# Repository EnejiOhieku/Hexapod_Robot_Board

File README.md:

# 18-DOF Hexapod Robot Controller Board (Rev 3.0)

[-brightgreen.svg)](reports/Hexapod_Robot_Board-erc.rpt)
[-brightgreen.svg)](reports/Hexapod_Robot_Board-drc.rpt)

A production-ready, high-power 4-layer robotics controller PCB designed for an **18-DOF Hexapod Robot**. Rev 3.0 is a major architectural upgrade introducing a **dedicated Vision Coprocessor** (second ESP32-S3-WROOM-1U-N8R8), a **BQ25886 2S LiPo fast charger** (replaces TP5100), **triple South-edge USB Type-C ports** (dedicated charging, main MCU, and vision MCU), an **OV3660/OV2640 DVP camera interface** with a 1–3W illumination LED driver, a **Sipeed MaixSense A010 3D ToF** sensor on a fully isolated 5V rail, a **dedicated Vision 3.3V ultra-low-noise LDO**, and an **external power switch connector**. The locomotion subsystem retains the proven dual 5A XL4015 buck split-rail architecture and dual PCA9685 uncrossed PWM routing.

---

## 3D Board Previews

---

## System Architecture (Rev 3.0)

```mermaid
flowchart TD
    subgraph Power["Power & Battery Management"]
        J_CHG["USB Type-C (J_CHG) — Dedicated 2S Charger"] --> U2["BQ25886 2S LiPo Charger (8.4V / 1.5A)"]
        BAT["2S LiPo Battery (XT30PW, South Edge)"] --> SW["Main Power Switch (SW_PWR)"]
        U2 --> BAT
        SW --> VBAT_SW["Switched Battery Bus (VBAT_SW)"]
        VBAT_SW --> BUCK_L["Left Buck (XL4015, 5V / 5A) — U3_L"]
        VBAT_SW --> BUCK_R["Right Buck (XL4015, 5V / 5A) — U3_R"]
        VBAT_SW --> U4["Main 3.3V LDO (AP2112K / AMS1117-3.3) — U4"]
        VBAT_SW --> U_LDO_VIS["Vision 3.3V LDO (AMS1117-3.3) — U_LDO_VIS"]
        VBAT_SW --> U_REG_5V_TOF["Dedicated 5V ToF Regulator (AMS1117-5.0) — U_REG_5V_TOF"]
        VBAT_SW --> DIV["Battery Voltage Divider (R_DIV1 / R_DIV2)"]
    end

    subgraph Locomotion["Main Locomotion Controller (U1 — ESP32-S3-WROOM-1U)"]
        J_USB_MAIN["USB Type-C (J2) — Native USB / JTAG"] --> U1["ESP32-S3-WROOM-1U (Top-Right Edge, IPEX U.FL)"]
        U4 --> U1
        U1 -- "I2C (GPIO1/41)" --> U5["PCA9685 Left (0x40) — U5"]
        U1 -- "I2C (GPIO1/41)" --> U6["PCA9685 Right (0x41) — U6"]
        U1 -- "I2C (GPIO1/41)" --> U7["MPU-6050 6-Axis IMU (Centre, 0x68) — U7"]
        U7 -- "MPU_INT (GPIO10)" --> U1
        DIV -- "ADC (GPIO5)" --> U1
        U1 -- "GPIO48" --> LED_RGB_MAIN["WS2812B-2020 Status NeoPixel"]
    end

    subgraph Vision["Vision Coprocessor (U8 — ESP32-S3-WROOM-1U-N8R8)"]
        J_USB_VIS["USB Type-C (J3) — Vision USB / JTAG"] --> U8["ESP32-S3-WROOM-1U-N8R8 (Top-Left Edge, IPEX U.FL)"]
        U_LDO_VIS --> U8
        U8 -- "24-Pin 8-bit DVP (GPIO6-13, 15-18)" --> CAM["OV3660 / OV2640 Camera (J_CAM)"]
        U8 -- "SCCB I2C1 (GPIO4/5)" --> CAM
        U8 -- "UART1 (GPIO1/2)" --> TOF["Sipeed MaixSense A010 3D ToF (J_TOF)"]
        U8 -- "GPIO3 → R_CAM_LED → Q_CAM_LED" --> CAM_LED["1–3W Camera LED (J_CAM_LED)"]
        U_REG_5V_TOF -- "+5V_TOF (Isolated from Servos)" --> TOF
    end

    U1 <==>|"Inter-MCU Full-Duplex UART (GPIO43/44) + Frame Sync IRQ"| U8

    subgraph Servos["Servo Actuation (Split Left/Right Rails)"]
        BUCK_L --> V_SERVO_L["V_SERVO_L Plane (In2.Cu West)"]
        BUCK_R --> V_SERVO_R["V_SERVO_R Plane (In2.Cu East)"]
        U5 -- "PWM 0–11" --> SL["Left Legs 4, 5, 6 (9 Servos) + AUX 4–6"]
        U6 -- "PWM 0–11" --> SR["Right Legs 1, 2, 3 (9 Servos) + AUX 1–3"]
        V_SERVO_L --> SL
        V_SERVO_R --> SR
    end
```

---

## Key Hardware Features

### Dual-MCU Architecture
- **Main Locomotion MCU (`U1`)**: ESP32-S3-WROOM-1U — Dual-core Xtensa LX7 @ 240 MHz, 2.4 GHz Wi-Fi, BLE 5, 16 MB Flash. Placed on the **Top-Right edge** (`X=88.0, Y=2.5 mm`) with IPEX U.FL antenna facing North.
- **Vision Coprocessor (`U8`)**: ESP32-S3-WROOM-1U-N8R8 — Identical SoC, 8 MB PSRAM (Octal), pin-compatible with Zephyr's `esp32s3_eye` board definition. Placed on the **Top-Left edge** (`X=22.0, Y=2.5 mm`) with IPEX U.FL facing North.
- **Inter-MCU Link**: Full-duplex UART (`U1` GPIO43/44 ↔ `U8` GPIO43/44) at up to 3 Mbps, plus hardware Frame Sync / Alert IRQ (`U8` GPIO21 → `U1` GPIO4).

### Vision & Perception
- **Camera Interface**: 24-pin DVP FPC connector (`J_CAM`, top-centre `X=55.0, Y≈-11.0 mm`, rotated 180°) for OV3660 (3 MP) or OV2640 (2 MP). SCCB I²C via 4.7 kΩ pull-ups (`R_CAM_SCL`, `R_CAM_SDA`).
- **3D ToF Sensor**: Sipeed MaixSense A010 connector (`J_TOF`) at `(5.0, -11.0) mm`, powered by an isolated `+5V_TOF` linear rail with >60 dB PSRR to eliminate servo switching noise.
- **Camera Illumination**: 1–3 W white LED driver via AO3400A N-MOSFET (`Q_CAM_LED`), gate driven by Vision GPIO3 through 100 Ω series (`R_CAM_LED`) + 10 kΩ pull-down (`R_PD_CAM_LED`). External LED connector: `J_CAM_LED`.
- **Status NeoPixel**: WS2812B-2020 (`LED_RGB_MAIN`) driven by Main MCU GPIO48 via 330 Ω damping resistor (`R_NEO`).

### Power Architecture
| Rail | Source | Voltage | Max Current | Consumer |
|:---|:---|:---|:---|:---|
| `+VBAT` | 2S LiPo XT30PW | 6.0–8.4 V | 20 A peak | Raw battery |
| `VBAT_SW` | SW_PWR / J_SW_EXT | 6.0–8.4 V | 15 A | All regulators |
| `V_SERVO_L` | XL4015 Buck L (`U3_L`) | 5.0 V | 5 A cont. / 6 A pk | Left legs + AUX 4–6 |
| `V_SERVO_R` | XL4015 Buck R (`U3_R`) | 5.0 V | 5 A cont. / 6 A pk | Right legs + AUX 1–3 |
| `+3V3` | AP2112K LDO (`U4`) | 3.3 V | 600 mA | Main MCU, PCA9685s, IMU |
| `+3V3_VIS` | AMS1117-3.3 (`U_LDO_VIS`) | 3.3 V | 800 mA | Vision MCU, camera |
| `+5V_TOF` | AMS1117-5.0 (`U_REG_5V_TOF`) | 5.0 V | 800 mA | MaixSense A010 ToF (isolated) |
| `VBUS` | USB-C (`J_CHG`) | 5.0 V | 2.0 A | BQ25886 charger input |

- **Battery Management**: BQ25886 (VQFN-24) 2S LiPo fast charger — replaces TP5100. Supports USB BC1.2 detection, USB OTG boost, PowerPath management. Charge/standby LEDs: `LED_CHG`, `LED_FULL`.
- **External Power Switch**: 2-pin header `J_SW_EXT` allows robot chassis-mounted latching switch to gate `VBAT_SW`. Battery charges safely with electronics fully off.

### Triple South-Edge USB-C
All three USB-C receptacles co-located along the South board edge for a single chassis port bay cutout:
1. **`J_CHG` (`J1`, X≈37 mm)** — Dedicated 2S fast charger input. Zero data lines.
2. **`J_USB_MAIN` (`J2`, X≈95.5 mm)** — Main ESP32-S3 native USB / JTAG / gait telemetry.
3. **`J_USB_VISION` (`J3`, X≈84 mm)** — Vision ESP32-S3 native USB / JTAG / video stream.

### Inertial Measurement Unit
- **MPU-6050** (`U7`) at exact geometric centre of mass (`X=55.0, Y=45.0 mm`) with hardware interrupt to Main MCU GPIO10.

### Physical Specifications
- **Dimensions**: 110.0 × 90.0 mm, 3.0 mm corner radii.
- **Mounting**: 4× M3 holes (3.2 mm drill / 6.0 mm pad) at `(5,5)`, `(105,5)`, `(5,85)`, `(105,85)` mm.
- **Stackup**: 4-layer — `F.Cu` signals/PDN · `In1.Cu` solid GND · `In2.Cu` split `V_SERVO` planes · `B.Cu` GND flood/signals.

---

## Servo Channel Mapping

| Joint / Channel | Header | Controller | Ch | I²C Addr | Rail |
|:---|:---|:---|:---|:---|:---|
| **Right Front (RF) Coxa** | `J_L1_C` | PCA9685 Right (`U6`) | PWM 0 | `0x41` | `V_SERVO_R` |
| **Right Front (RF) Femur** | `J_L1_F` | PCA9685 Right (`U6`) | PWM 1 | `0x41` | `V_SERVO_R` |
| **Right Front (RF) Tibia** | `J_L1_T` | PCA9685 Right (`U6`) | PWM 2 | `0x41` | `V_SERVO_R` |
| **Right Middle (RM) Coxa** | `J_L2_C` | PCA9685 Right (`U6`) | PWM 3 | `0x41` | `V_SERVO_R` |
| **Right Middle (RM) Femur** | `J_L2_F` | PCA9685 Right (`U6`) | PWM 4 | `0x41` | `V_SERVO_R` |
| **Right Middle (RM) Tibia** | `J_L2_T` | PCA9685 Right (`U6`) | PWM 5 | `0x41` | `V_SERVO_R` |
| **Right Rear (RR) Coxa** | `J_L3_C` | PCA9685 Right (`U6`) | PWM 6 | `0x41` | `V_SERVO_R` |
| **Right Rear (RR) Femur** | `J_L3_F` | PCA9685 Right (`U6`) | PWM 7 | `0x41` | `V_SERVO_R` |
| **Right Rear (RR) Tibia** | `J_L3_T` | PCA9685 Right (`U6`) | PWM 8 | `0x41` | `V_SERVO_R` |
| **Left Front (LF) Coxa** | `J_L4_C` | PCA9685 Left (`U5`) | PWM 0 | `0x40` | `V_SERVO_L` |
| **Left Front (LF) Femur** | `J_L4_F` | PCA9685 Left (`U5`) | PWM 1 | `0x40` | `V_SERVO_L` |
| **Left Front (LF) Tibia** | `J_L4_T` | PCA9685 Left (`U5`) | PWM 2 | `0x40` | `V_SERVO_L` |
| **Left Middle (LM) Coxa** | `J_L5_C` | PCA9685 Left (`U5`) | PWM 3 | `0x40` | `V_SERVO_L` |
| **Left Middle (LM) Femur** | `J_L5_F` | PCA9685 Left (`U5`) | PWM 4 | `0x40` | `V_SERVO_L` |
| **Left Middle (LM) Tibia** | `J_L5_T` | PCA9685 Left (`U5`) | PWM 5 | `0x40` | `V_SERVO_L` |
| **Left Rear (LR) Coxa** | `J_L6_C` | PCA9685 Left (`U5`) | PWM 6 | `0x40` | `V_SERVO_L` |
| **Left Rear (LR) Femur** | `J_L6_F` | PCA9685 Left (`U5`) | PWM 7 | `0x40` | `V_SERVO_L` |
| **Left Rear (LR) Tibia** | `J_L6_T` | PCA9685 Left (`U5`) | PWM 8 | `0x40` | `V_SERVO_L` |
| **Auxiliary PWM 1–3** | `J_AUX1–3` | PCA9685 Right (`U6`) | PWM 9–11 | `0x41` | `V_SERVO_R` |
| **Auxiliary PWM 4–6** | `J_AUX4–6` | PCA9685 Left (`U5`) | PWM 9–11 | `0x40` | `V_SERVO_L` |

---

## GPIO Assignments

### Main Locomotion MCU (`U1` — ESP32-S3-WROOM-1U)
| GPIO | Function | Direction | Connected To |
|:---|:---|:---|:---|
| GPIO1 | I2C SCL | Output | PCA9685 L/R, MPU-6050 |
| GPIO41 | I2C SDA | Bidirectional | PCA9685 L/R, MPU-6050 |
| GPIO4 | Frame Sync IRQ | Input | Vision MCU GPIO21 |
| GPIO5 | Battery ADC | Input | `R_DIV1`/`R_DIV2` voltage divider |
| GPIO6 | CHG_STAT | Input | BQ25886 `STAT` pin |
| GPIO7 | CHG_PG | Input | BQ25886 `PG` pin (Power Good) |
| GPIO10 | MPU_INT | Input | MPU-6050 INT |
| GPIO19/20 | USB D-/D+ | Bidirectional | `J_USB_MAIN` (J2) |
| GPIO43 | Inter-MCU TX | Output | Vision MCU GPIO44 |
| GPIO44 | Inter-MCU RX | Input | Vision MCU GPIO43 |
| GPIO48 | NeoPixel Data | Output | `R_NEO` → `LED_RGB_MAIN` |

### Vision Coprocessor (`U8` — ESP32-S3-WROOM-1U-N8R8)
| GPIO | Function | Direction | Connected To |
|:---|:---|:---|:---|
| GPIO1 | ToF UART RX | Input | A010 TX (UART1) |
| GPIO2 | ToF UART TX | Output | A010 RX (UART1) |
| GPIO3 | Camera LED PWM | Output | `R_CAM_LED` → `Q_CAM_LED` gate |
| GPIO4 | SCCB SDA (I2C1) | Bidirectional | Camera SIOD, 4.7 kΩ pull-up |
| GPIO5 | SCCB SCL (I2C1) | Output | Camera SIOC, 4.7 kΩ pull-up |
| GPIO6 | DVP VSYNC | Input | Camera VSYNC |
| GPIO7 | DVP HREF | Input | Camera HREF |
| GPIO8–13 | DVP D2–D7 | Input | Camera Y4–Y9 |
| GPIO15 | DVP XCLK | Output | Camera XCLK (10–24 MHz) |
| GPIO16–18 | DVP D0–D2 | Input | Camera Y2–Y4 |
| GPIO19/20 | USB D-/D+ | Bidirectional | `J_USB_VISION` (J3) |
| GPIO21 | Frame Sync IRQ | Output | Main MCU GPIO4 |
| GPIO38 | Camera PWDN | Output | Camera PWDN, 10 kΩ pull-down |
| GPIO43 | Inter-MCU TX | Output | Main MCU GPIO44 |
| GPIO44 | Inter-MCU RX | Input | Main MCU GPIO43 |

---

## Project Structure

```
Hexapod_Robot_Board/
├── Hexapod_Robot_Board.kicad_pro       # Master KiCad 10.0.6 project file
├── Hexapod_Robot_Board.kicad_sch       # Rev 3.0 schematic (dual-MCU, triple USB-C)
├── Hexapod_Robot_Board.kicad_pcb       # 4-layer routed PCB layout
├── Hexapod_Robot_Board.net             # Complete netlist (98 nets)
├── README.md                           # This document
├── 3dmodels/                           # Custom 3D STEP component packages
│   ├── ESP32-S3-WROOM-1U.step
│   ├── MPU-6050.step
│   ├── LED_WS2812B-2020.step
│   └── Hirose_FH12-24S-0.5SH_1x24-1MP_P0.50mm_Horizontal.step
├── fabrication/                        # Manufacturing deliverable package
│   ├── Hexapod_Robot_Board-gerbers.zip
│   ├── Hexapod_Robot_Board-cpl-jlcpcb.csv
│   ├── Hexapod_Robot_Board-bom-jlcpcb.csv
│   ├── Hexapod_Robot_Board.step
│   ├── Hexapod_Robot_Board_Schematic.pdf
│   └── *.png                           # 2D + 3D renders
├── reports/                            # Verification reports
│   ├── Hexapod_Robot_Board-drc.rpt
│   ├── Hexapod_Robot_Board-erc.rpt
│   └── Hexapod_Robot_Board-stats.txt
└── scripts/                            # Python automation suite
    ├── export_fabrication.py           # One-click manufacturing pipeline
    ├── run_final_perfect_route.py      # Freerouting solver
    └── README.md
```

---

## Verification & Compliance

- **ERC**: Passed — **0 errors, 0 warnings** ([`reports/Hexapod_Robot_Board-erc.rpt`](reports/Hexapod_Robot_Board-erc.rpt)).
- **DRC**: Passed — **0 violations, 0 unconnected items** ([`reports/Hexapod_Robot_Board-drc.rpt`](reports/Hexapod_Robot_Board-drc.rpt)).
- **Manufacturability**: JLCPCB / PCBWay 4-layer standard constraints (0.15 mm clearance, 0.20 mm min track, 0.30 mm min drill, 45° mitered geometry).

---

## Revision History

| Rev | Date | Summary |
|:---|:---|:---|
| **3.0** | 2026-10-04 | Vision Coprocessor (ESP32-S3-WROOM-1U-N8R8), BQ25886 2S charger, triple South USB-C, DVP camera, MaixSense A010 ToF on isolated +5V rail, dedicated Vision 3.3V LDO, camera LED driver, inter-MCU UART link, external power switch header, WS2812B NeoPixel. Schematic/PCB annotated and synced. |
| **2.0** | 2026-10-01 | ESP32-S3-WROOM-1U, dual XL4015 5A buck split rails, MPU-6050 at CoM, South-edge USB-C charging via TP5100, dual PCA9685 uncrossed PWM, 4-layer routing, 0 DRC/ERC. |
| **1.0** | 2026-09-28 | Initial 18-DOF hexapod controller. ESP32-S3, single buck, TP5100 charger, dual PCA9685. |

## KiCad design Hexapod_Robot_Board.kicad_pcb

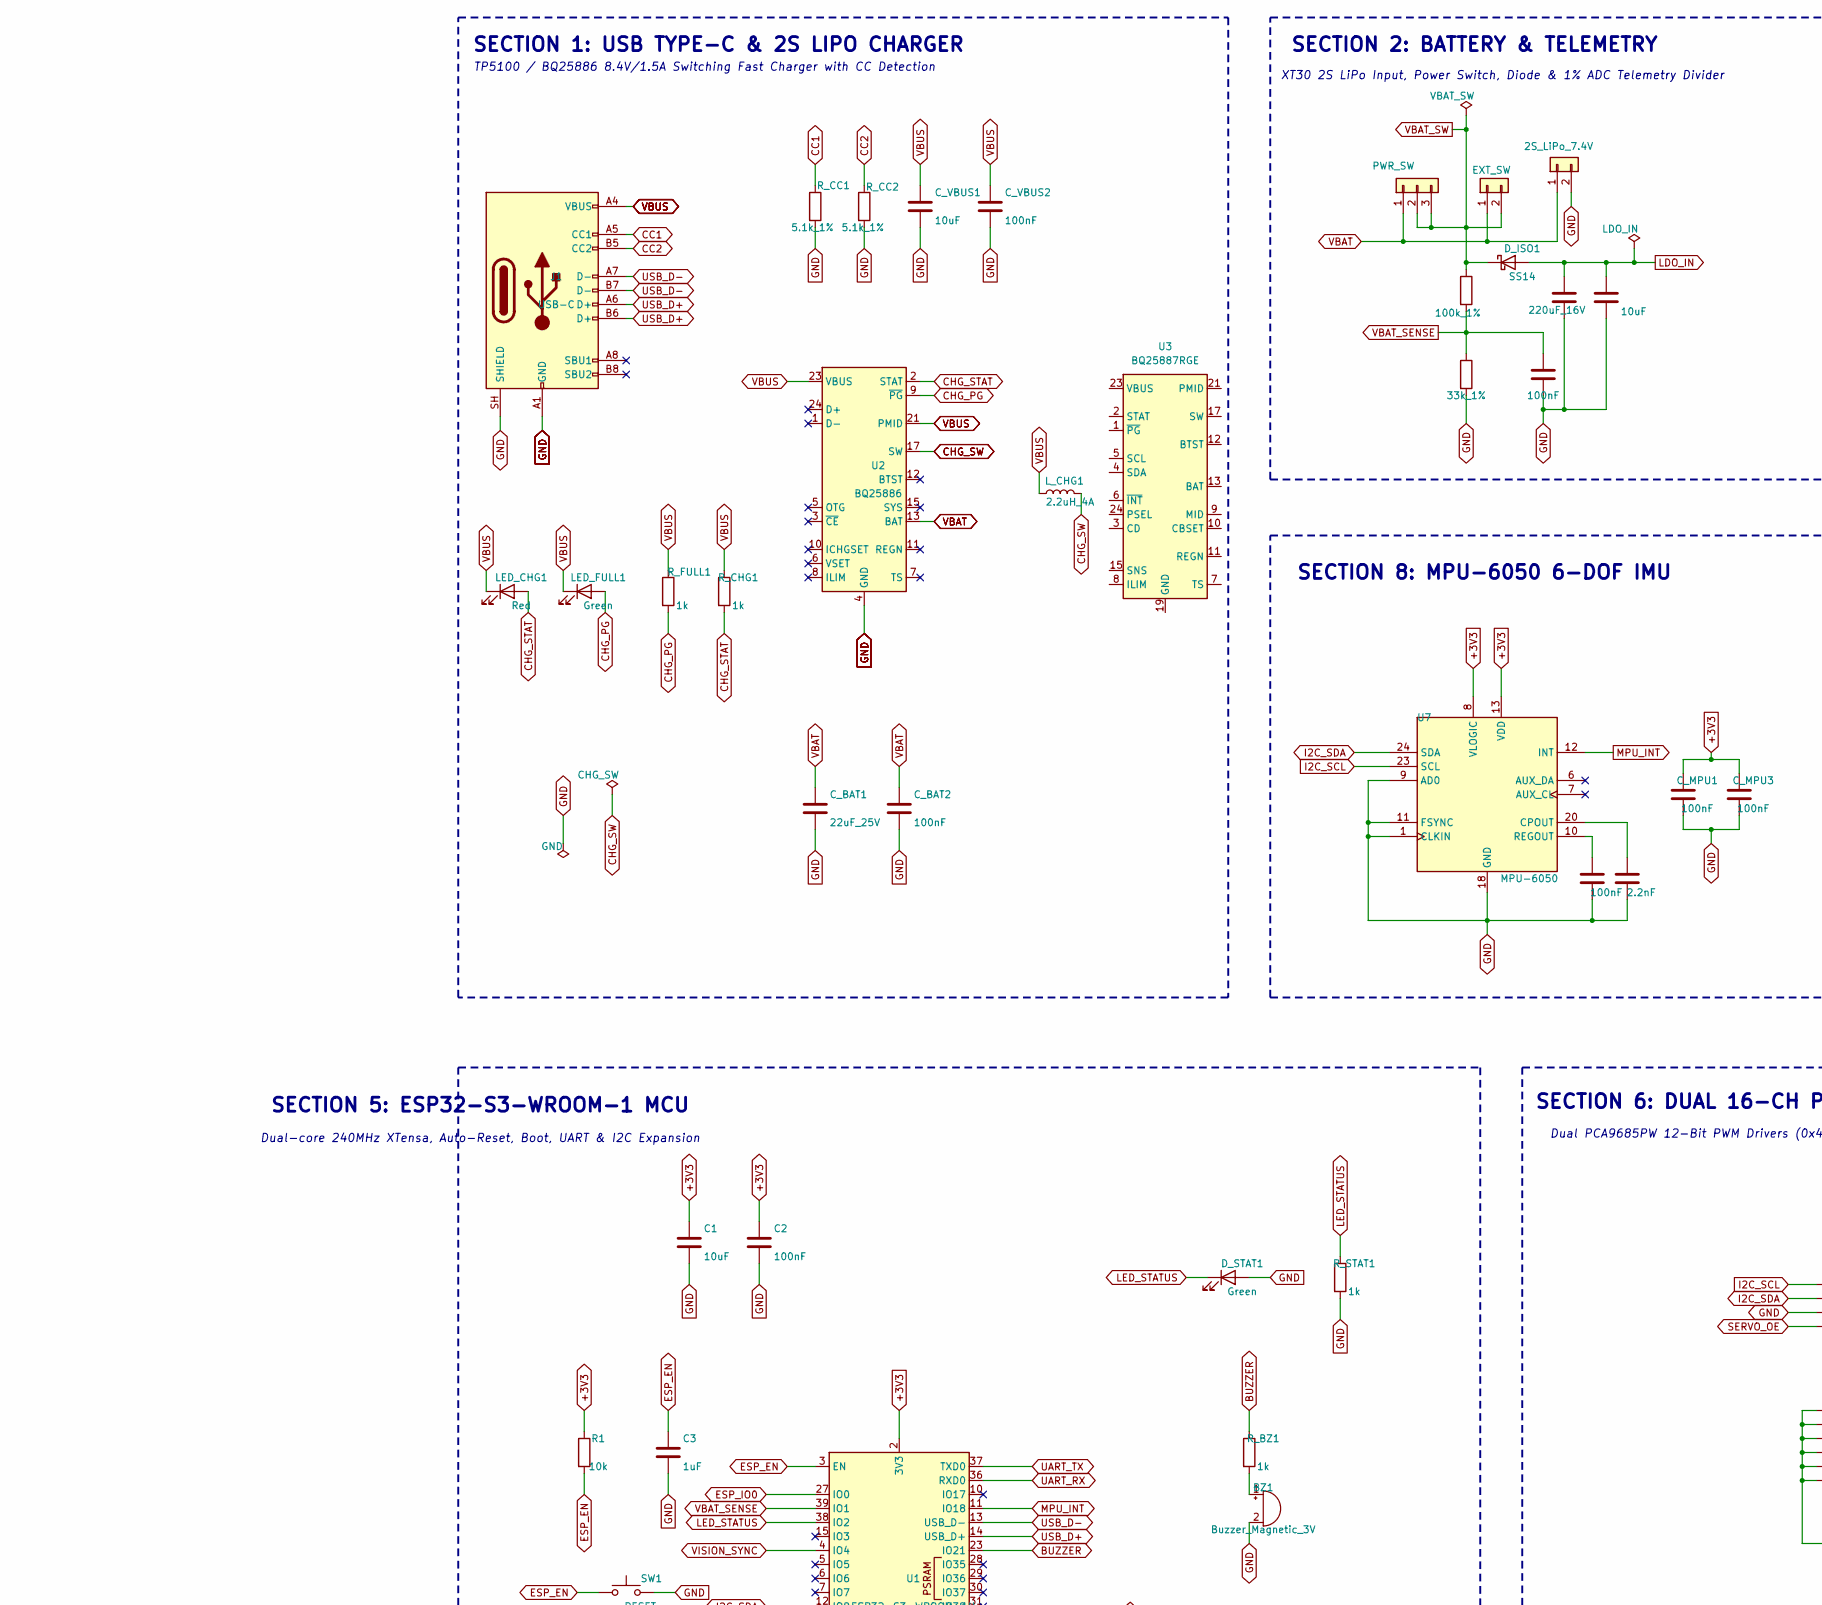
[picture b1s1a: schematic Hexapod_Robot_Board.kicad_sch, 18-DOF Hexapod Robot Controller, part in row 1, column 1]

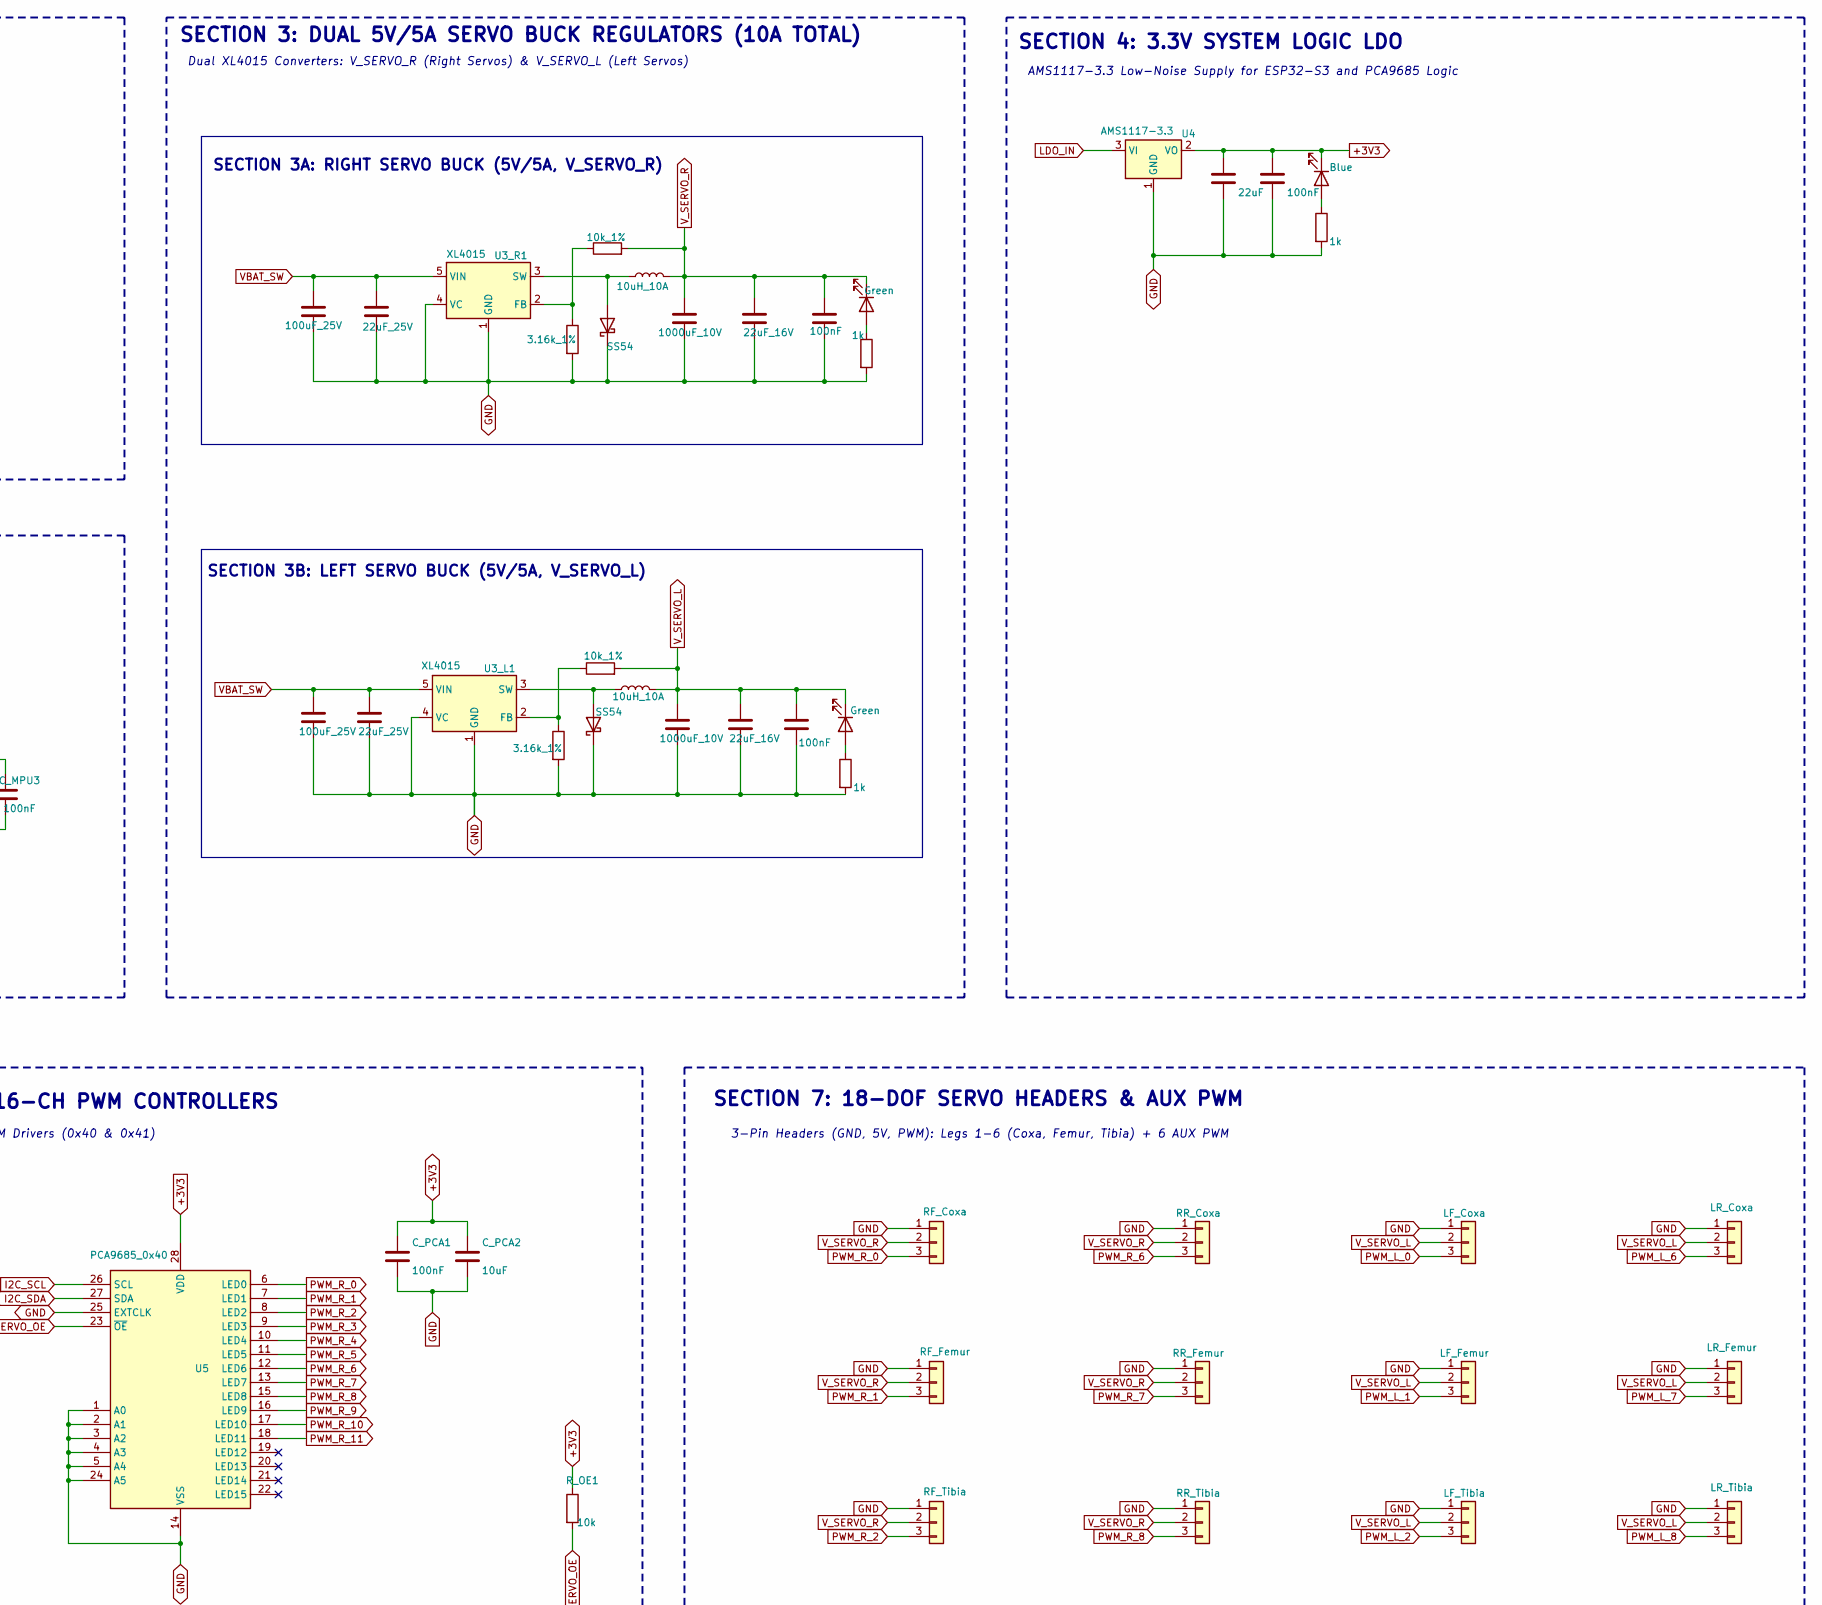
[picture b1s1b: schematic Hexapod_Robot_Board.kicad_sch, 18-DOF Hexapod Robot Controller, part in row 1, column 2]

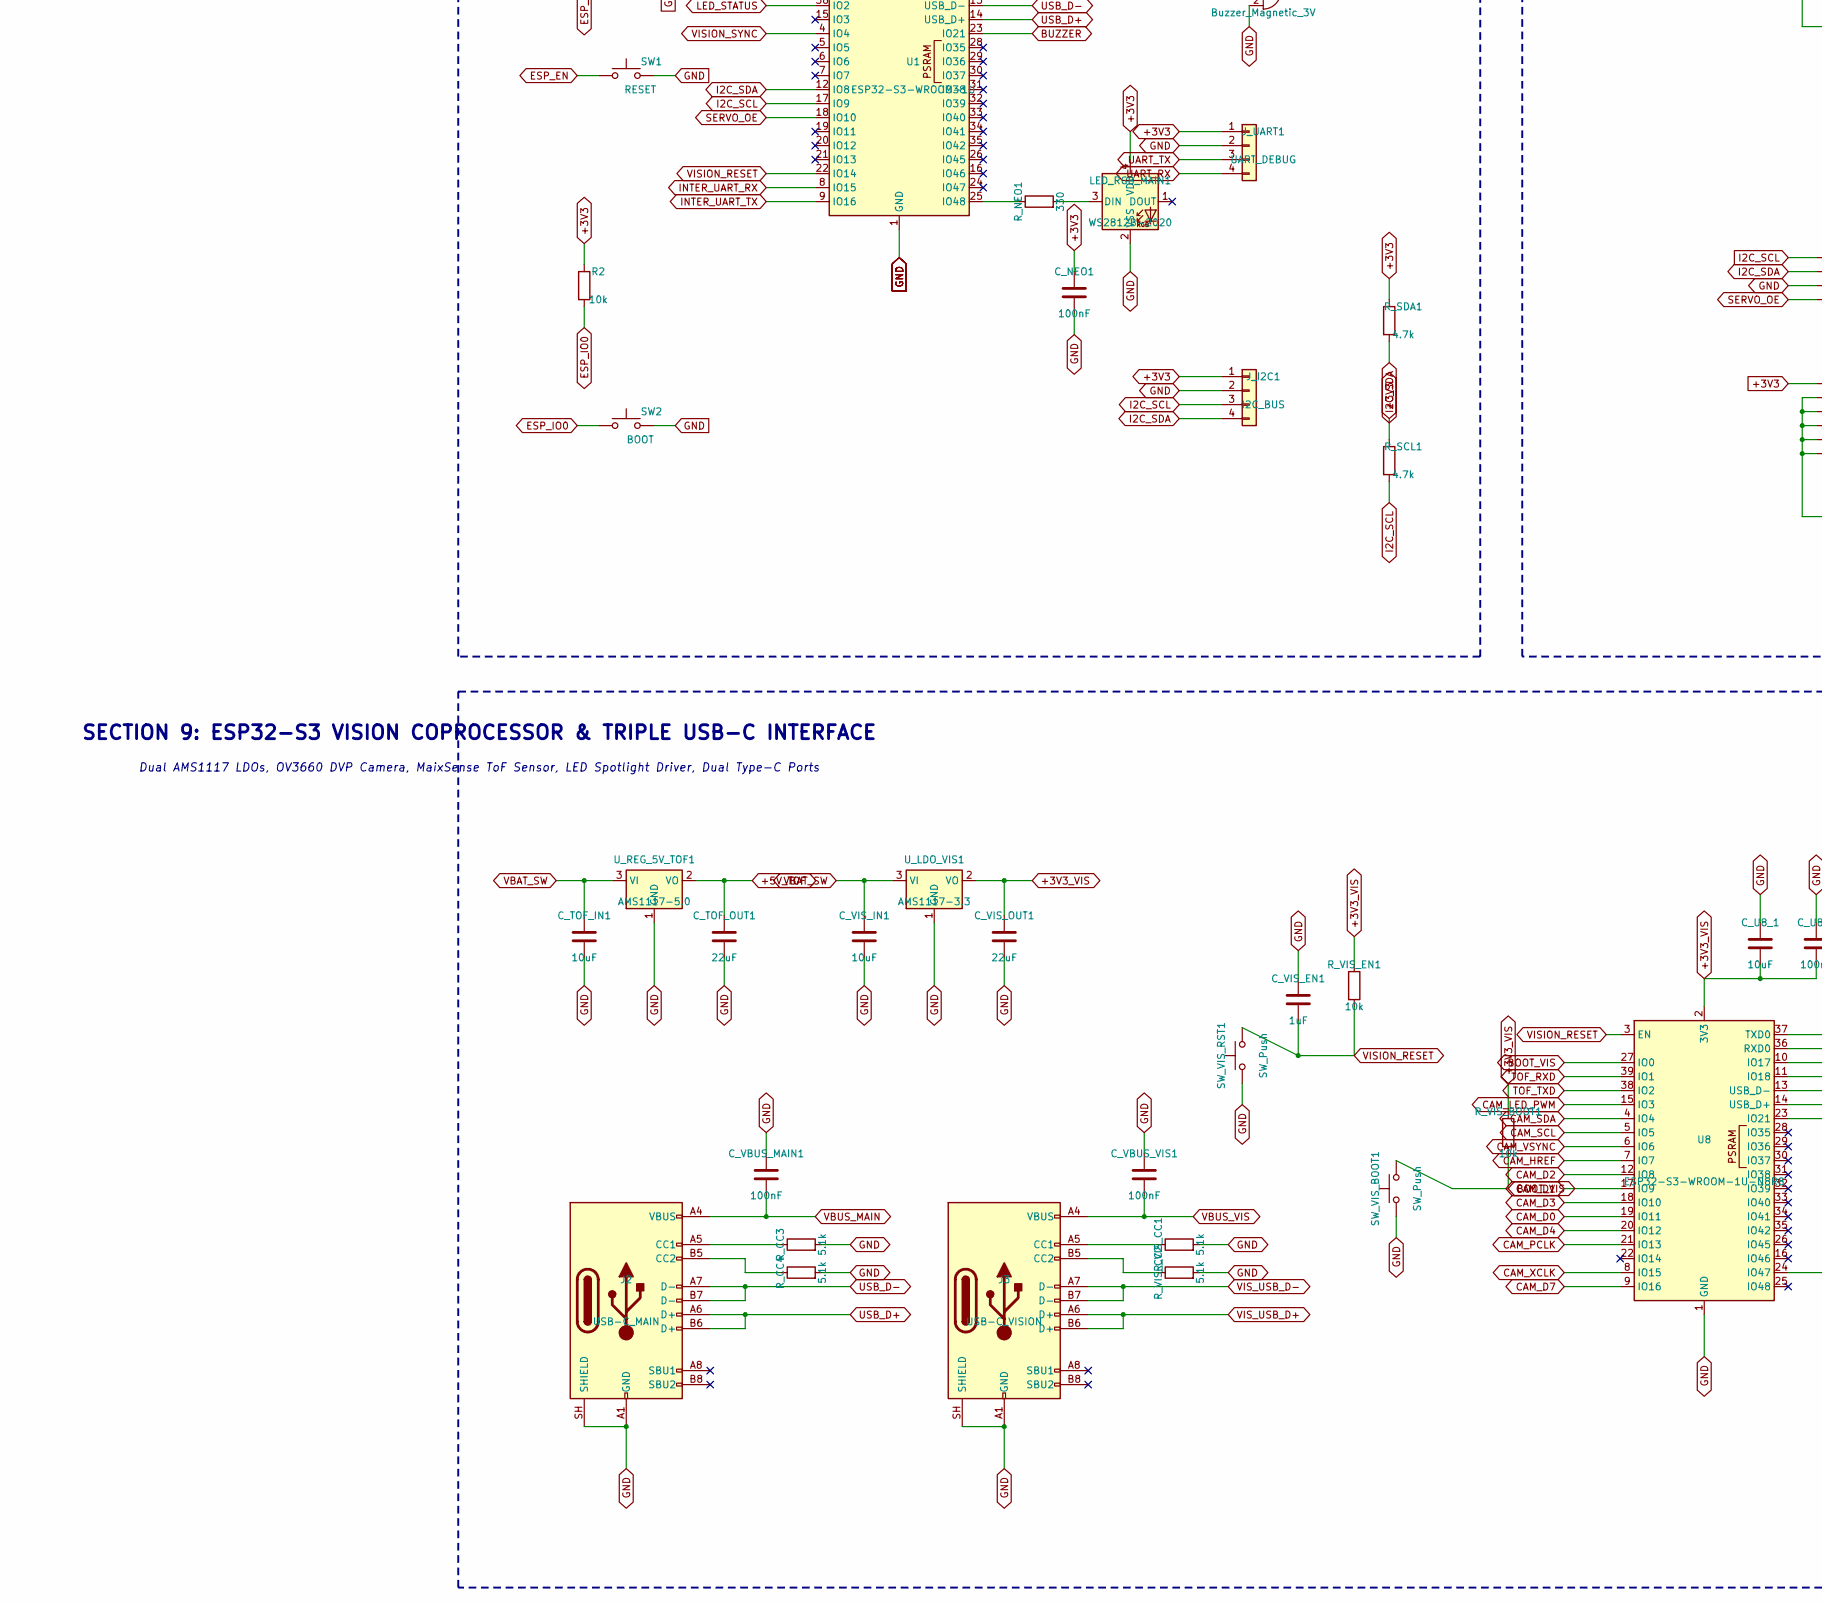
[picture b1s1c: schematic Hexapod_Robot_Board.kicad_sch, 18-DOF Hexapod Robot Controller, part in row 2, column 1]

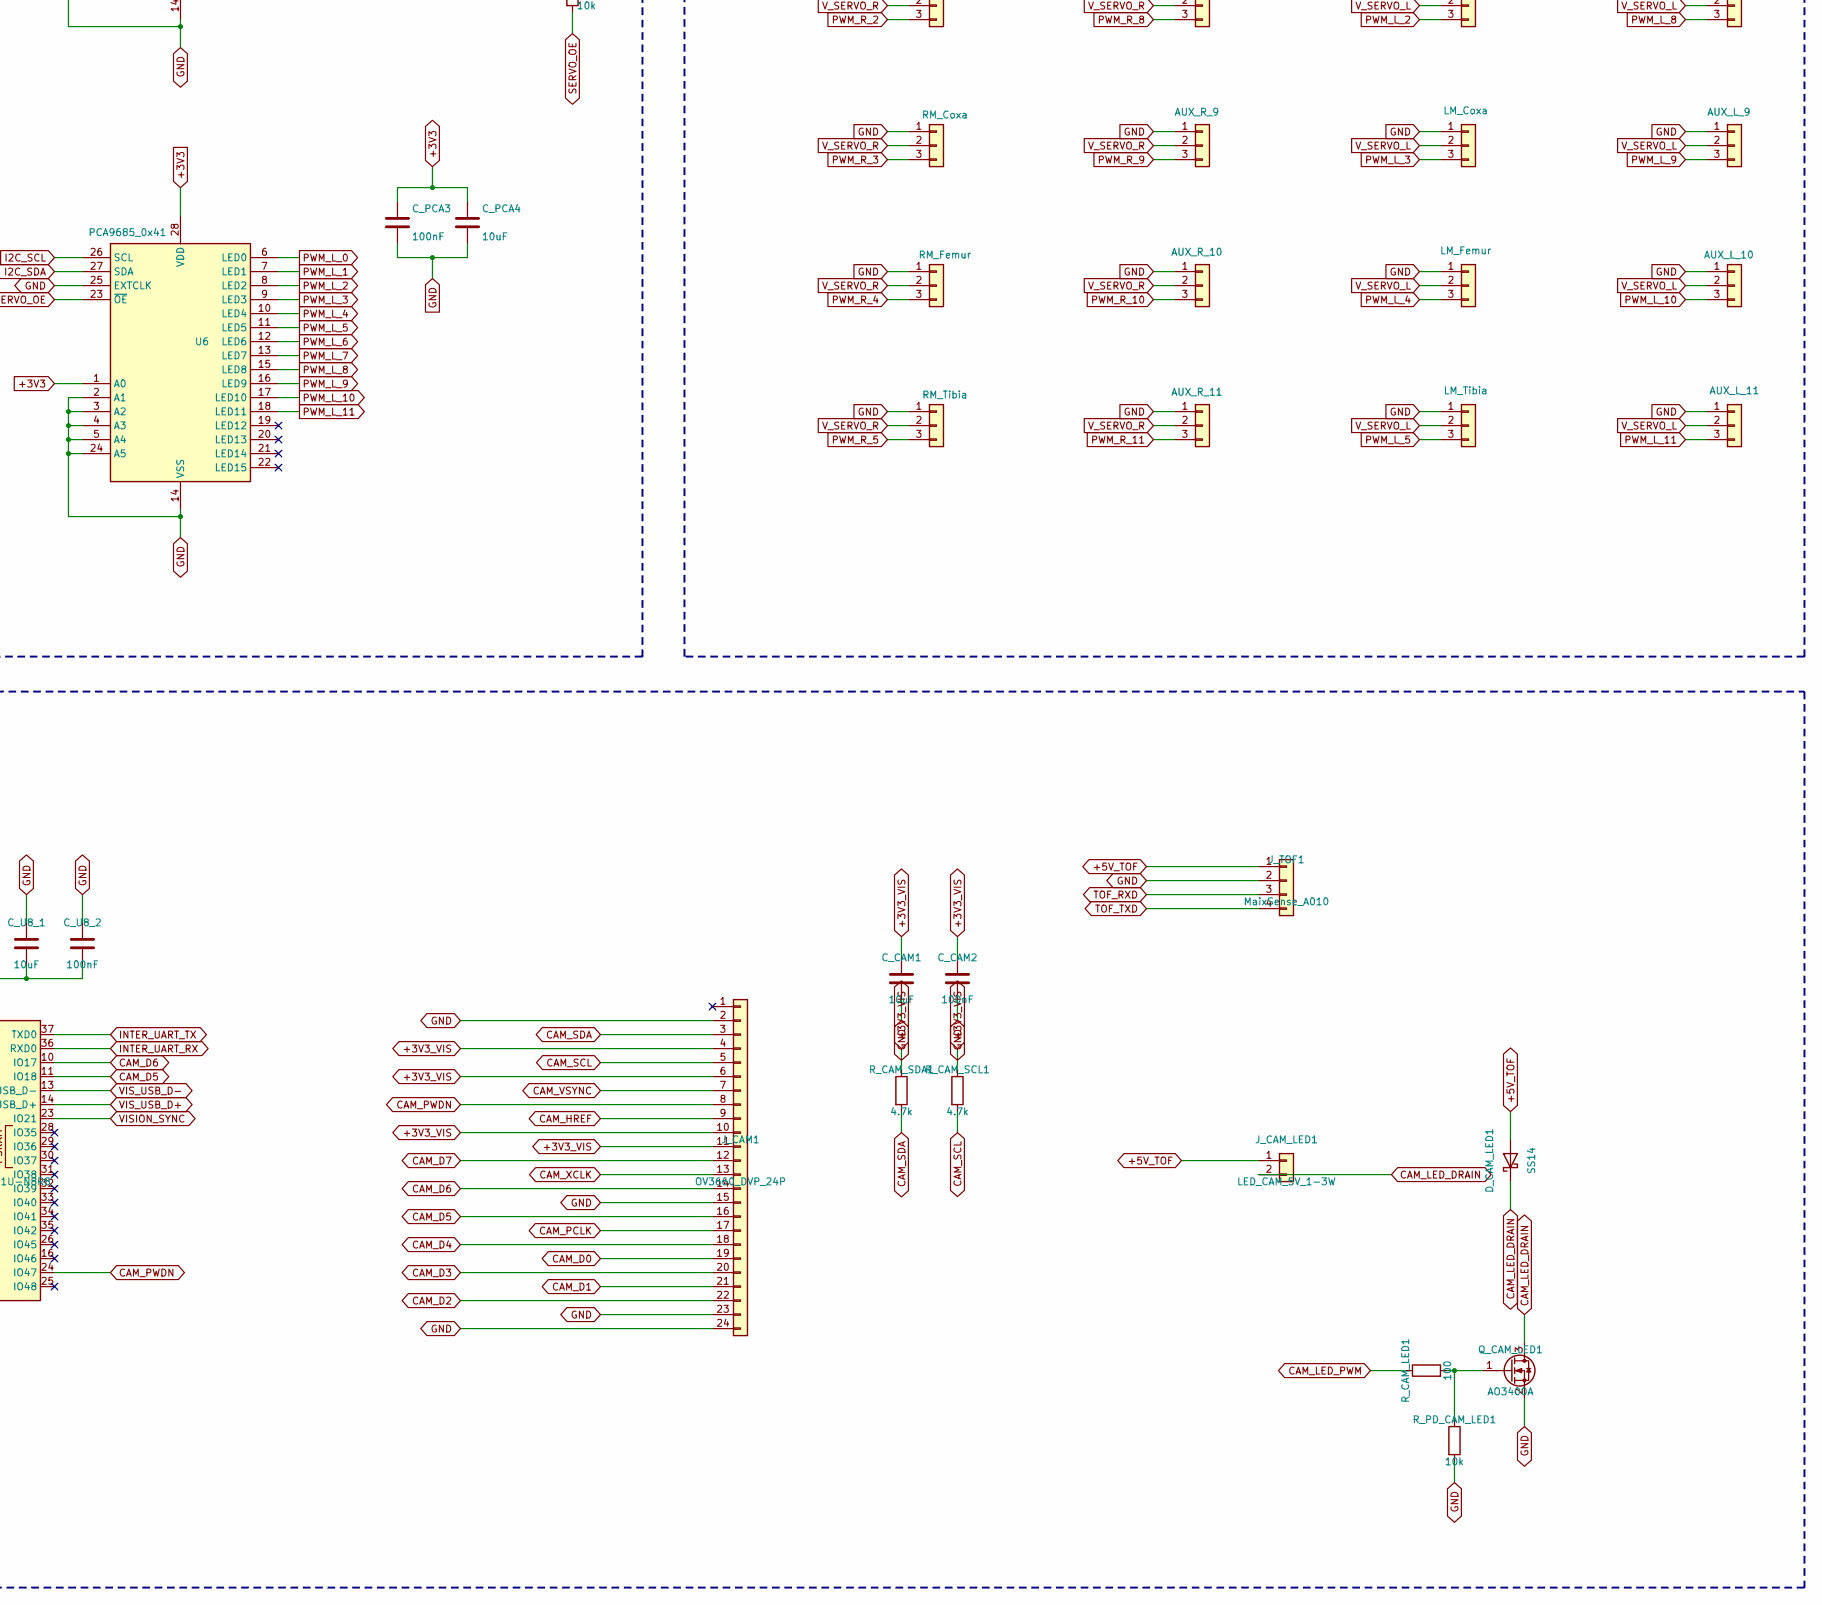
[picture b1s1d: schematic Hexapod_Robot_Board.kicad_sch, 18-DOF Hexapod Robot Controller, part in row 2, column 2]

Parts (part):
BZ1: Buzzer_Magnetic_3V; MagneticBuzzer_Kingstate_KCG0601
C1: 10uF; C_0805_2012Metric
C2: 100nF; C_0603_1608Metric
C3: 1uF; C_0603_1608Metric
C_3V3_1: 22uF; C_0805_2012Metric
C_3V3_2: 100nF; C_0603_1608Metric
C_BAT1: 22uF_25V; C_1206_3216Metric
C_BAT2: 100nF; C_0603_1608Metric
C_CAM1: 10uF; C_0805_2012Metric
C_CAM2: 100nF; C_0603_1608Metric
C_DIV1: 100nF; C_0603_1608Metric
C_IN1_L1, C_IN1_R1: 100uF_25V; CP_Radial_D8.0mm_P3.50mm
C_IN2_L1, C_IN2_R1: 22uF_25V; C_1206_3216Metric
C_ISO1: 220uF_16V; CP_Radial_D8.0mm_P3.50mm
C_ISO2: 10uF; C_0805_2012Metric
C_MPU1, C_MPU2, C_MPU3: 100nF; C_0603_1608Metric
C_MPU5: 2.2nF; C_0603_1608Metric
C_NEO1: 100nF; C_0603_1608Metric
C_OUT1_L1, C_OUT1_R1: 1000uF_10V; CP_Radial_D8.0mm_P3.50mm
C_OUT2_L1, C_OUT2_R1: 22uF_16V; C_1206_3216Metric
C_OUT3_L1, C_OUT3_R1: 100nF; C_0603_1608Metric
C_PCA1, C_PCA3: 100nF; C_0603_1608Metric
C_PCA2, C_PCA4: 10uF; C_0805_2012Metric
C_TOF_IN1: 10uF; C_0805_2012Metric
C_TOF_OUT1: 22uF; C_0805_2012Metric
C_U8_1: 10uF; C_0805_2012Metric
C_U8_2: 100nF; C_0603_1608Metric
C_VBUS1: 10uF; C_0805_2012Metric
C_VBUS2: 100nF; C_0603_1608Metric
C_VBUS_MAIN1: 100nF; C_0603_1608Metric
C_VBUS_VIS1: 100nF; C_0603_1608Metric
C_VIS_EN1: 1uF; C_0603_1608Metric
C_VIS_IN1: 10uF; C_0805_2012Metric
C_VIS_OUT1: 22uF; C_0805_2012Metric
D_CAM_LED1: SS14; D_SOD-123
D_CATCH_L1: SS54; D_SMC
D_CATCH_R1: SS54; D_SMC
D_ISO1: SS14; D_SOD-123
D_STAT1: Green; LED_0603_1608Metric
J1: USB-C; USB_C_Receptacle_HCTL_HC-TYPE-C-16P-01A
J2: USB-C_MAIN; USB_C_Receptacle_HCTL_HC-TYPE-C-16P-01A
J3: USB-C_VISION; USB_C_Receptacle_HCTL_HC-TYPE-C-16P-01A
J_AUX1: AUX_R_9; PinHeader_1x03_P2.54mm_Vertical
J_AUX2: AUX_R_10; PinHeader_1x03_P2.54mm_Vertical
J_AUX3: AUX_R_11; PinHeader_1x03_P2.54mm_Vertical
J_AUX4: AUX_L_9; PinHeader_1x03_P2.54mm_Vertical
J_AUX5: AUX_L_10; PinHeader_1x03_P2.54mm_Vertical
J_AUX6: AUX_L_11; PinHeader_1x03_P2.54mm_Vertical
J_BAT1: 2S_LiPo_7.4V; AMASS_XT30PW-M_1x02_P2.50mm_Horizontal
J_CAM1: OV3660_DVP_24P; Hirose_FH12-24S-0.5SH_1x24-1MP_P0.50mm_Horizontal
J_CAM_LED1: LED_CAM_5V_1-3W; PinHeader_1x02_P2.54mm_Vertical
J_I2C1: I2C_BUS; PinHeader_1x04_P2.54mm_Vertical
J_L1_C1: RF_Coxa; PinHeader_1x03_P2.54mm_Vertical
J_L1_F1: RF_Femur; PinHeader_1x03_P2.54mm_Vertical
J_L1_T1: RF_Tibia; PinHeader_1x03_P2.54mm_Vertical
J_L2_C1: RM_Coxa; PinHeader_1x03_P2.54mm_Vertical
J_L2_F1: RM_Femur; PinHeader_1x03_P2.54mm_Vertical
J_L2_T1: RM_Tibia; PinHeader_1x03_P2.54mm_Vertical
J_L3_C1: RR_Coxa; PinHeader_1x03_P2.54mm_Vertical
J_L3_F1: RR_Femur; PinHeader_1x03_P2.54mm_Vertical
J_L3_T1: RR_Tibia; PinHeader_1x03_P2.54mm_Vertical
J_L4_C1: LF_Coxa; PinHeader_1x03_P2.54mm_Vertical
J_L4_F1: LF_Femur; PinHeader_1x03_P2.54mm_Vertical
J_L4_T1: LF_Tibia; PinHeader_1x03_P2.54mm_Vertical
J_L5_C1: LM_Coxa; PinHeader_1x03_P2.54mm_Vertical
J_L5_F1: LM_Femur; PinHeader_1x03_P2.54mm_Vertical
J_L5_T1: LM_Tibia; PinHeader_1x03_P2.54mm_Vertical
J_L6_C1: LR_Coxa; PinHeader_1x03_P2.54mm_Vertical
J_L6_F1: LR_Femur; PinHeader_1x03_P2.54mm_Vertical
J_L6_T1: LR_Tibia; PinHeader_1x03_P2.54mm_Vertical
J_SW_EXT1: EXT_SW; PinHeader_1x02_P2.54mm_Vertical
J_TOF1: MaixSense_A010; PinHeader_1x04_P2.54mm_Vertical
J_UART1: UART_DEBUG; PinHeader_1x04_P2.54mm_Vertical
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
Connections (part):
+3V3: C1.1, C2.1, C_3V3_1.1, C_3V3_2.1, C_MPU1.1, C_MPU3.1, C_NEO1.1, C_PCA1.1, C_PCA2.1, C_PCA3.1, C_PCA4.1, J_I2C1.1, J_UART1.1, LED_3V3.1 (K), LED_RGB_MAIN1.4 (VDD), R1.1, R2.1, R_OE1.1, R_SCL1.1, R_SDA1.1, U1.2 (3V3), U4.2 (VO), U5.28 (VDD), U6.1 (A0), U6.28 (VDD), U7.8 (VLOGIC), U7.13 (VDD)
+3V3_VIS: C_CAM1.1, C_CAM2.1, C_U8_1.2, C_U8_2.2, C_VIS_OUT1.1, J_CAM1.4, J_CAM1.6, J_CAM1.10, J_CAM1.11, R_CAM_SCL1.1, R_CAM_SDA1.1, R_VIS_BOOT1.1, R_VIS_EN1.1, U8.2 (3V3), U_LDO_VIS1.2 (VO)
+5V_TOF: C_TOF_OUT1.1, D_CAM_LED1.2 (A), J_CAM_LED1.1, J_TOF1.1, U_REG_5V_TOF1.2 (VO)
BOOT_VIS: R_VIS_BOOT1.2, SW_VIS_BOOT1.2, U8.27 (IO0)
BUZZER: R_BZ1.1, U1.23 (IO21)
CAM_D0: J_CAM1.19, U8.19 (IO11)
CAM_D1: J_CAM1.21, U8.17 (IO9)
CAM_D2: J_CAM1.22, U8.12 (IO8)
CAM_D3: J_CAM1.20, U8.18 (IO10)
CAM_D4: J_CAM1.18, U8.20 (IO12)
CAM_D5: J_CAM1.16, U8.11 (IO18)
CAM_D6: J_CAM1.14, U8.10 (IO17)
CAM_D7: J_CAM1.12, U8.9 (IO16)
CAM_HREF: J_CAM1.9, U8.7 (IO7)
CAM_LED_DRAIN: D_CAM_LED1.1 (K), J_CAM_LED1.2, Q_CAM_LED1.3 (D)
CAM_LED_PWM: R_CAM_LED1.1, U8.15 (IO3)
CAM_PCLK: J_CAM1.17, U8.21 (IO13)
CAM_PWDN: J_CAM1.8, U8.24 (IO47)
CAM_SCL: J_CAM1.5, R_CAM_SCL1.2, U8.5 (IO5)
CAM_SDA: J_CAM1.3, R_CAM_SDA1.2, U8.4 (IO4)
CAM_VSYNC: J_CAM1.7, U8.6 (IO6)
CAM_XCLK: J_CAM1.13, U8.8 (IO15)
CC1: J1.A5 (CC1), R_CC1.1
CC2: J1.B5 (CC2), R_CC2.1
CHG_PG: LED_FULL1.2 (A), R_FULL1.2, U2.9 (~PG)
CHG_STAT: LED_CHG1.2 (A), R_CHG1.2, U2.2 (STAT)
CHG_SW: L_CHG1.2, U2.17 (SW), U2.18 (SW)
ESP_EN: C3.1, R1.2, SW1.1, U1.3 (EN)
ESP_IO0: R2.2, SW2.1, U1.27 (IO0)
GND: BZ1.2 (-), C1.2, C2.2, C3.2, C_3V3_1.2, C_3V3_2.2, C_BAT1.2, C_BAT2.2, C_CAM1.2, C_CAM2.2, C_DIV1.2, C_IN1_L1.2, C_IN1_R1.2, C_IN2_L1.2, C_IN2_R1.2, C_ISO1.2, C_ISO2.2, C_MPU1.2, C_MPU2.2, C_MPU3.2, C_MPU5.2, C_NEO1.2, C_OUT1_L1.2, C_OUT1_R1.2, C_OUT2_L1.2, C_OUT2_R1.2, C_OUT3_L1.2, C_OUT3_R1.2, C_PCA1.2, C_PCA2.2, C_PCA3.2, C_PCA4.2, C_TOF_IN1.2, C_TOF_OUT1.2, C_U8_1.1, C_U8_2.1, C_VBUS1.2, C_VBUS2.2, C_VBUS_MAIN1.1, C_VBUS_VIS1.1, C_VIS_EN1.1, C_VIS_IN1.2, C_VIS_OUT1.2, D_CATCH_L1.1 (K), D_CATCH_R1.1 (K), D_STAT1.2 (A), J1.A1 (GND), J1.A12 (GND), J1.B1 (GND), J1.B12 (GND), J1.SH (SHIELD), J2.A1 (GND), J2.A12 (GND), J2.B1 (GND), J2.B12 (GND), J2.SH (SHIELD), J3.A1 (GND), J3.A12 (GND), J3.B1 (GND), J3.B12 (GND), J3.SH (SHIELD), J_AUX1.1, J_AUX2.1, J_AUX3.1, J_AUX4.1, J_AUX5.1, J_AUX6.1, J_BAT1.2, J_CAM1.2, J_CAM1.15, J_CAM1.23, J_CAM1.24, J_I2C1.2, J_L1_C1.1, J_L1_F1.1, J_L1_T1.1, J_L2_C1.1, J_L2_F1.1, J_L2_T1.1, J_L3_C1.1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
I2C_SCL: J_I2C1.3, R_SCL1.2, U1.17 (IO9), U5.26 (SCL), U6.26 (SCL), U7.23 (SCL)
I2C_SDA: J_I2C1.4, R_SDA1.2, U1.12 (IO8), U5.27 (SDA), U6.27 (SDA), U7.24 (SDA)
INTER_UART_RX: U1.8 (IO15), U8.36 (RXD0)
INTER_UART_TX: U1.9 (IO16), U8.37 (TXD0)
LDO_IN: C_ISO1.1, C_ISO2.1, D_ISO1.2 (A), U4.3 (VI)
LED_STATUS: D_STAT1.1 (K), R_STAT1.1, U1.38 (IO2)
MPU_INT: U1.11 (IO18), U7.12 (INT)
unnamed: BZ1.1 (+), R_BZ1.2
unnamed: D_CATCH_L1.2 (A), L_SERVO_L1.1, U3_L1.3 (SW)
unnamed: D_CATCH_R1.2 (A), L_SERVO_R1.1, U3_R1.3 (SW)
unnamed: J2.A5 (CC1), R_CC3.1
unnamed: J2.B5 (CC2), R_CC4.1
unnamed: J3.A5 (CC1), R_VIS_CC1.1
unnamed: J3.B5 (CC2), R_VIS_CC2.1
unnamed: LED_3V3.2 (A), R_3V3_LED1.1
unnamed: LED_L1.2 (A), R_LED_L1.1
unnamed: LED_R1.2 (A), R_LED_R1.1
unnamed: LED_RGB_MAIN1.3 (DIN), R_NEO1.2
unnamed: Q_CAM_LED1.1 (G), R_CAM_LED1.2, R_PD_CAM_LED1.1
unnamed: R_NEO1.1, U1.25 (IO48)
unnamed: U3.13 (BAT), U3.14 (BAT)
unnamed: U3.15 (SNS), U3.16 (SNS)
unnamed: U3.17 (SW), U3.18 (SW)
unnamed: U3.19 (GND), U3.20 (GND), U3.25 (GND)
unnamed: U3.21 (PMID), U3.22 (PMID)
unnamed: R_FB1_L1.1, R_FB2_L1.1, U3_L1.2 (FB)
unnamed: R_FB1_R1.1, R_FB2_R1.1, U3_R1.2 (FB)
unnamed: C_MPU5.1, U7.20 (CPOUT)
unnamed: C_MPU2.1, U7.10 (REGOUT)
PWM_L_0: J_L4_C1.3, U6.6 (LED0)
PWM_L_1: J_L4_F1.3, U6.7 (LED1)
PWM_L_2: J_L4_T1.3, U6.8 (LED2)
PWM_L_3: J_L5_C1.3, U6.9 (LED3)
PWM_L_4: J_L5_F1.3, U6.10 (LED4)
PWM_L_5: J_L5_T1.3, U6.11 (LED5)
PWM_L_6: J_L6_C1.3, U6.12 (LED6)
PWM_L_7: J_L6_F1.3, U6.13 (LED7)
PWM_L_8: J_L6_T1.3, U6.15 (LED8)
PWM_L_9: J_AUX4.3, U6.16 (LED9)
PWM_L_10: J_AUX5.3, U6.17 (LED10)
PWM_L_11: J_AUX6.3, U6.18 (LED11)
PWM_R_0: J_L1_C1.3, U5.6 (LED0)
PWM_R_1: J_L1_F1.3, U5.7 (LED1)
PWM_R_2: J_L1_T1.3, U5.8 (LED2)
PWM_R_3: J_L2_C1.3, U5.9 (LED3)
PWM_R_4: J_L2_F1.3, U5.10 (LED4)
PWM_R_5: J_L2_T1.3, U5.11 (LED5)
PWM_R_6: J_L3_C1.3, U5.12 (LED6)
PWM_R_7: J_L3_F1.3, U5.13 (LED7)
PWM_R_8: J_L3_T1.3, U5.15 (LED8)
PWM_R_9: J_AUX1.3, U5.16 (LED9)
PWM_R_10: J_AUX2.3, U5.17 (LED10)
PWM_R_11: J_AUX3.3, U5.18 (LED11)
SERVO_OE: R_OE1.2, U1.18 (IO10), U5.23 (~OE), U6.23 (~OE)
TOF_RXD: J_TOF1.3, U8.39 (IO1)
TOF_TXD: J_TOF1.4, U8.38 (IO2)
UART_RX: J_UART1.4, U1.36 (RXD0)
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
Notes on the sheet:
SECTION 8: MPU-6050 6-DOF IMU
Dual XL4015 Converters: V_SERVO_R (Right Servos) & V_SERVO_L (Left Servos)
SECTION 9: ESP32-S3 VISION COPROCESSOR & TRIPLE USB-C INTERFACE
SECTION 4: 3.3V SYSTEM LOGIC LDO
TP5100 / BQ25886 8.4V/1.5A Switching Fast Charger with CC Detection
Dual PCA9685PW 12-Bit PWM Drivers (0x40 & 0x41)
SECTION 7: 18-DOF SERVO HEADERS & AUX PWM
Dual AMS1117 LDOs, OV3660 DVP Camera, MaixSense ToF Sensor, LED Spotlight Driver, Dual Type-C Ports
SECTION 1: USB TYPE-C & 2S LIPO CHARGER
SECTION 3A: RIGHT SERVO BUCK (5V/5A, V_SERVO_R)
SECTION 2: BATTERY & TELEMETRY
3-Pin Headers (GND, 5V, PWM): Legs 1-6 (Coxa, Femur, Tibia) + 6 AUX PWM
SECTION 5: ESP32-S3-WROOM-1 MCU
SECTION 6: DUAL 16-CH PWM CONTROLLERS
SECTION 3B: LEFT SERVO BUCK (5V/5A, V_SERVO_L)
AMS1117-3.3 Low-Noise Supply for ESP32-S3 and PCA9685 Logic
Dual-core 240MHz XTensa, Auto-Reset, Boot, UART & I2C Expansion
XT30 2S LiPo Input, Power Switch, Diode & 1% ADC Telemetry Divider
SECTION 3: DUAL 5V/5A SERVO BUCK REGULATORS (10A TOTAL)

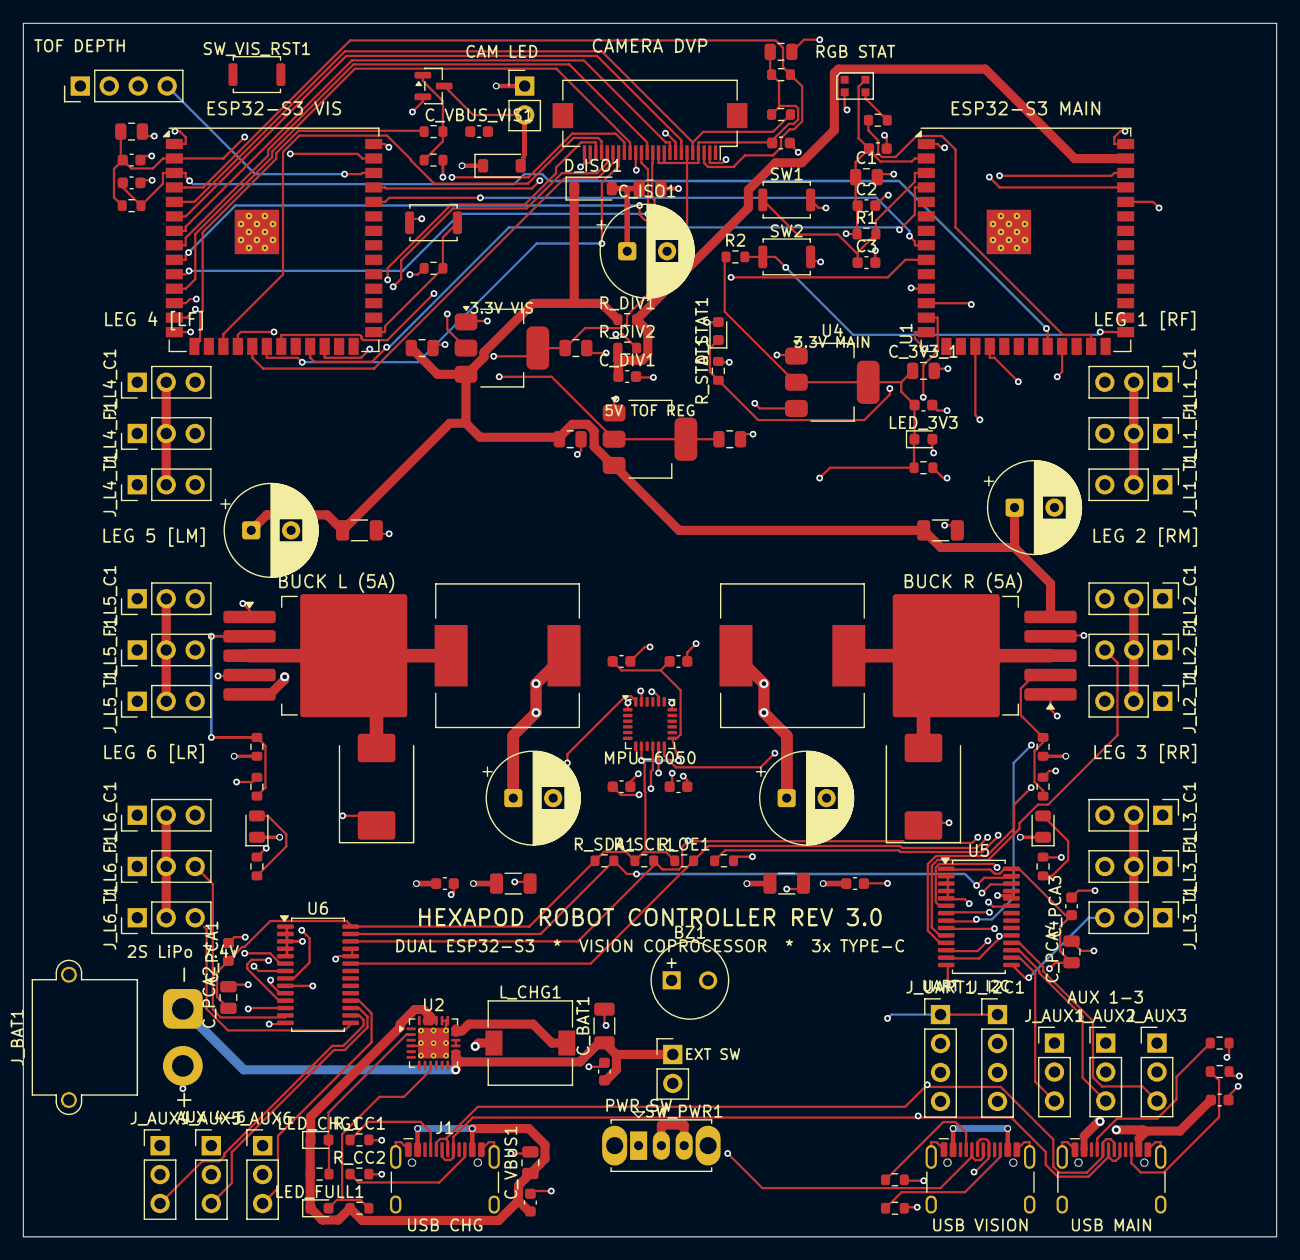
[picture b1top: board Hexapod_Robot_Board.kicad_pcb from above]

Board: 4 copper layers, 110.0 x 106.5 mm, 139 parts (0 on the bottom side), 97 nets.

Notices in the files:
README.md:
License: MIT
